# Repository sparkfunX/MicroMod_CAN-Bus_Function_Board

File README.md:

SparkX MicroMod CAN Bus Function Board
========================================

[*MicroMod CAN Bus Function Board (SPX-21775)*](https://www.sparkfun.com/products/21775)

Controller Area Network (CAN bus) continues to be a popular communication standard in all sorts of applications from passenger vehicles to lighting control and building automation. This MicroMod function board allows you to add CAN networking to your next MicroMod project. 

The CAN communications are handled by the MCP2515 stand-alone CAN controller paired up with an MCP2551 high-speed CAN transceiver. The MCP2515 is a very popular IC for CAN Bus, which means there are a variety of Arduino libraries already available. We quite like Sandeep Mistry's [arduino-CAN Library](https://github.com/sandeepmistry/arduino-CAN). If your processor board has a built-in CAN controller, however, you can change a solder jumper on the bottom of the board to address the CAN transceiver directly, bypassing the MCP2515.

Repository Contents
-------------------

* **/Hardware** - Eagle design files (.brd, .sch)
* **/Production** - Production panel files (.brd)

Documentation
--------------
  
* **[MCP2515 Datasheet](https://cdn.sparkfun.com/assets/1/0/e/4/0/MCP2515-Family-Data-Sheet-DS20001801K.pdf)** -MCP2515 Stand-Alone CAN Controller
* **[MCP2551 Datasheet](https://cdn.sparkfun.com/assets/8/d/9/b/8/20001667G.pdf)** -MCP2551 High-Speed CAN Transceiver
* **[Arduino Library](https://github.com/sandeepmistry/arduino-CAN)** -Sandeep Mistry's arduino-CAN library

License Information
-------------------

This product is _**open source**_! 

Please review the LICENSE.md file for license information. 

If you have any questions or concerns on licensing, please contact technical support on our [SparkFun forums](https://forum.sparkfun.com/viewforum.php?f=152).

Distributed as-is; no warranty is given.

- Your friends at SparkFun.

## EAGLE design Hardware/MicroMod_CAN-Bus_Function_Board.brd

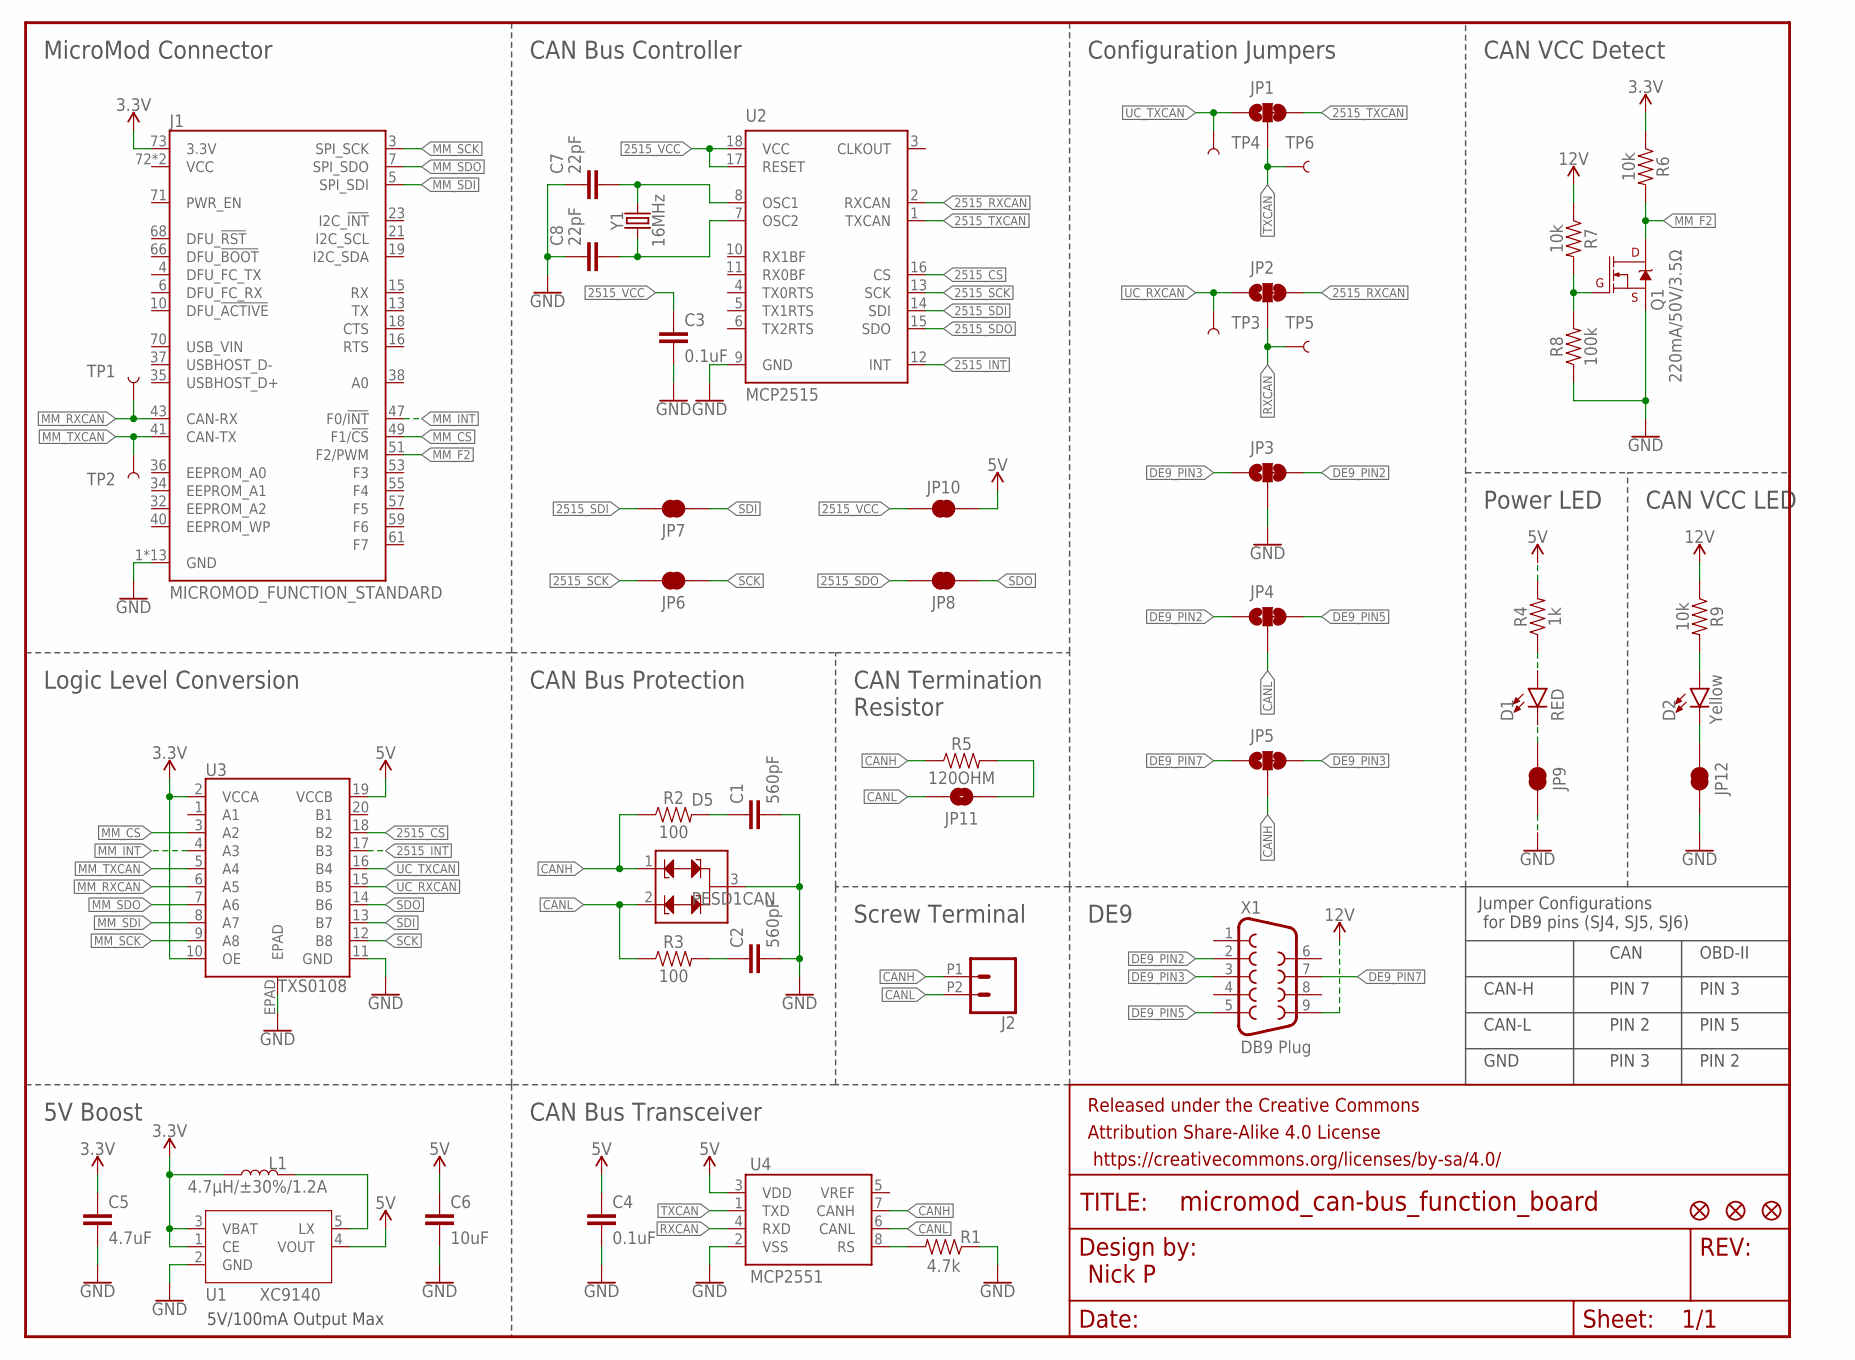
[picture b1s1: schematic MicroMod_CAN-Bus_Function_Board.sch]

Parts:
C1, C2: 560pF; 0603
C3, C4: 0.1uF; 0603
C5: 4.7uF; 0603
C6: 10uF; 0603
C7, C8: 22pF; 0603
D1: RED; LED-0603
D2: Yellow; LED-0603
D5: PESD1CAN; SOT23-3
FD1, FD2: FIDUCIAL1X2; FIDUCIAL-1X2
FD3: FIDUCIAL0.2MM; FIDUCIAL-0.2MM
FRAME1: FRAME-LETTER; CREATIVE_COMMONS
J1: MICROMOD_FUNCTION_STANDARD; M.2-CARD-E-22_FUNCTION_STANDARD
J2: CONN_022.54MM_SCREWTERM; 1X02_2.54_SCREWTERM
JP1, JP2, JP3, JP4, JP5: JUMPER-SMT_3_1-NC_TRACE_NO-SILK; SMT-JUMPER_3_1-NC_TRACE_NO-SILK
JP6, JP7, JP8, JP9, JP10, JP12: JUMPER-SMT_2_NC_TRACE_NO-SILK; SMT-JUMPER_2_NC_TRACE_NO-SILK
JP11: JUMPER-SMT_2_NO_NO-SILK; SMT-JUMPER_2_NO_NO-SILK
L1: 4.7µH/±30%/1.2A; INDUCTOR_4.7UH
Q1: 220mA/50V/3.5Ω; SOT23-3
R1: 4.7k; 0603
R2, R3: 100; 0603
R4: 1k; 0603
R5: 120OHM; 0603
R6, R7, R9: 10k; 0603
R8: 100k; 0603
TP1, TP2, TP3, TP4, TP5, TP6: TEST-POINT3; PAD.03X.03
U1: XC9140; SOT23-5
U2: MCP2515; SO18W
U3: TXS0108; VFQFN-20
U4: MCP2551; SO08
X1: DB9 Plug; DB9_MALE
Y1: 16MHz; CRYSTAL-SMD-2.0X1.6MM

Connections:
3.3V: C5.1, J1.73 (3.3V), L1.P$2 (2), R6.1, U1.1 (CE), U1.3 (VBAT), U3.2 (VCCA), U3.10 (OE)
5V: C4.1, C6.1, JP10.2, R4.2, U1.4 (VOUT), U3.19 (VCCB), U4.3 (VDD)
12V: R7.1, R9.1, X1.9
2515_CS: U2.16 (CS), U3.18 (B2)
2515_INT: U2.12 (INT), U3.17 (B3)
2515_RXCAN: JP2.3, U2.2 (RXCAN)
2515_SCK: JP6.2, U2.13 (SCK)
2515_SDI: JP7.2, U2.14 (SDI)
2515_SDO: JP8.2, U2.15 (SDO)
2515_TXCAN: JP1.3, U2.1 (TXCAN)
2515_VCC: C3.1, JP10.1, U2.17 (RESET), U2.18 (VCC)
CANH: D5.1, J2.P1 (1), JP5.2, R2.1, R5.1, U4.7 (CANH)
CANL: D5.2, J2.P2 (2), JP4.2, JP11.2, R3.1, U4.6 (CANL)
DE9_PIN2: JP3.3, JP4.1, X1.2
DE9_PIN3: JP3.1, JP5.3, X1.3
DE9_PIN5: JP4.3, X1.5
DE9_PIN7: JP5.1, X1.7
GND: C1.2, C2.2, C3.2, C4.2, C5.2, C6.2, C7.1, C8.1, D5.3, J1.1 (GND), J1.2 (GND), J1.8 (GND), J1.33 (GND), J1.39 (GND), J1.45 (GND), J1.75 (GND), J1.GND1 (GND), J1.GND2 (GND), J1.GND3 (GND), J1.GND4 (GND), J1.GND5 (GND), J1.GND6 (GND), JP3.2, JP9.2, JP12.2, Q1.2 (S), R1.1, R8.1, U1.2 (GND), U2.9 (GND), U3.11 (GND), U4.2 (VSS)
MM_CS: J1.49 (F1/!CS!), U3.3 (A2)
MM_F2: J1.51 (F2/PWM), Q1.3 (D), R6.2
MM_INT: J1.47 (F0/!INT!), U3.4 (A3)
MM_RXCAN: J1.43 (CAN-RX), TP1.1, U3.6 (A5)
MM_SCK: J1.3 (SPI_SCK), U3.9 (A8)
MM_SDI: J1.5 (SPI_SDI), U3.8 (A7)
MM_SDO: J1.7 (SPI_SDO), U3.7 (A6)
MM_TXCAN: J1.41 (CAN-TX), TP2.1, U3.5 (A4)
unnamed: C1.1, R2.2
unnamed: C2.1, R3.2
unnamed: C7.2, U2.8 (OSC1), Y1.3 (2)
unnamed: L1.P$1 (1), U1.5 (LX)
unnamed: C8.2, U2.7 (OSC2), Y1.1
unnamed: JP11.1, R5.2
unnamed: D1.C, JP9.1
unnamed: D1.A, R4.1
unnamed: R1.2, U4.8 (RS)
unnamed: Q1.1 (G), R7.2, R8.2
unnamed: D2.A, R9.2
unnamed: D2.C, JP12.1
RXCAN: JP2.2, TP5.1, U4.4 (RXD)
SCK: JP6.1, U3.12 (B8)
SDI: JP7.1, U3.13 (B7)
SDO: JP8.1, U3.14 (B6)
TXCAN: JP1.2, TP6.1, U4.1 (TXD)
UC_RXCAN: JP2.1, TP3.1, U3.15 (B5)
UC_TXCAN: JP1.1, TP4.1, U3.16 (B4)

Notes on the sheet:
CAN
OBD-II
CAN-H
CAN-L
GND
PIN 5
PIN 2
PIN 3
PIN 7
Jumper Configurations for DB9 pins (SJ4, SJ5, SJ6)
5V/100mA Output Max
MicroMod Connector
CAN Bus Controller
Configuration Jumpers
CAN VCC Detect
Power LED
DE9
Screw Terminal
CAN Termination Resistor
CAN Bus Protection
Logic Level Conversion
5V Boost
CAN Bus Transceiver
CAN VCC LED
Nick P

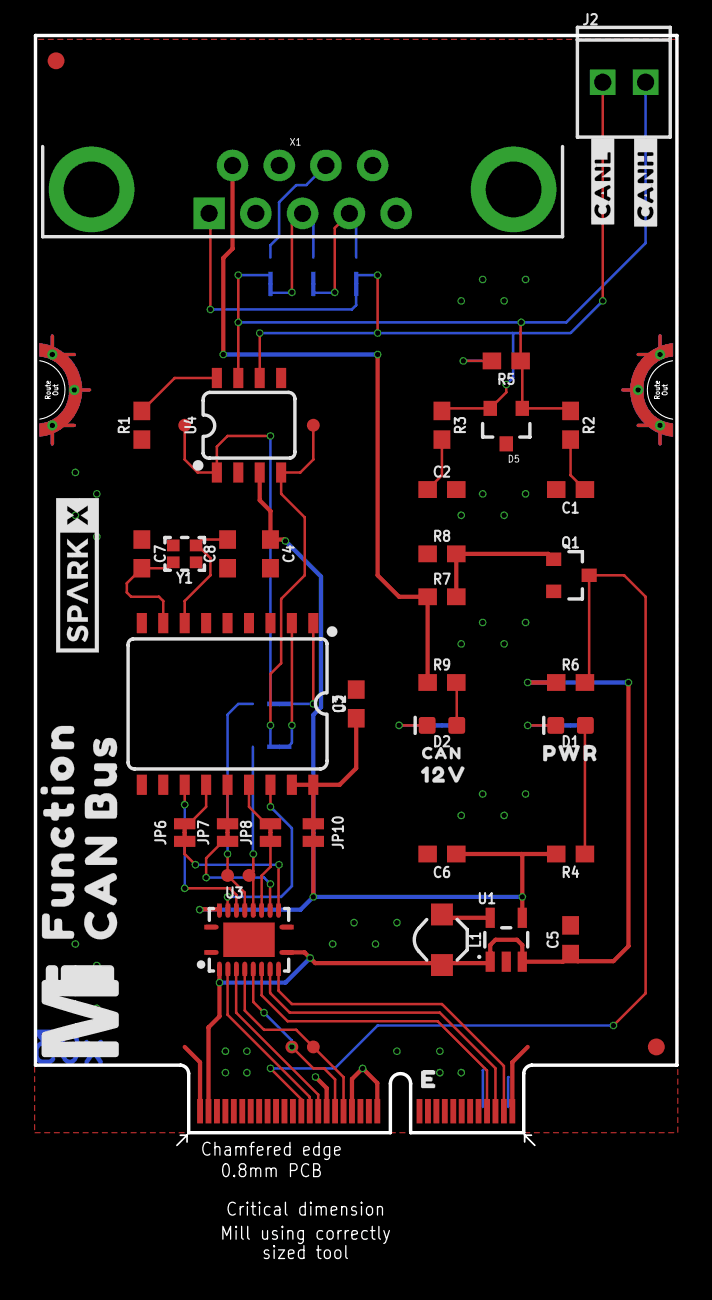
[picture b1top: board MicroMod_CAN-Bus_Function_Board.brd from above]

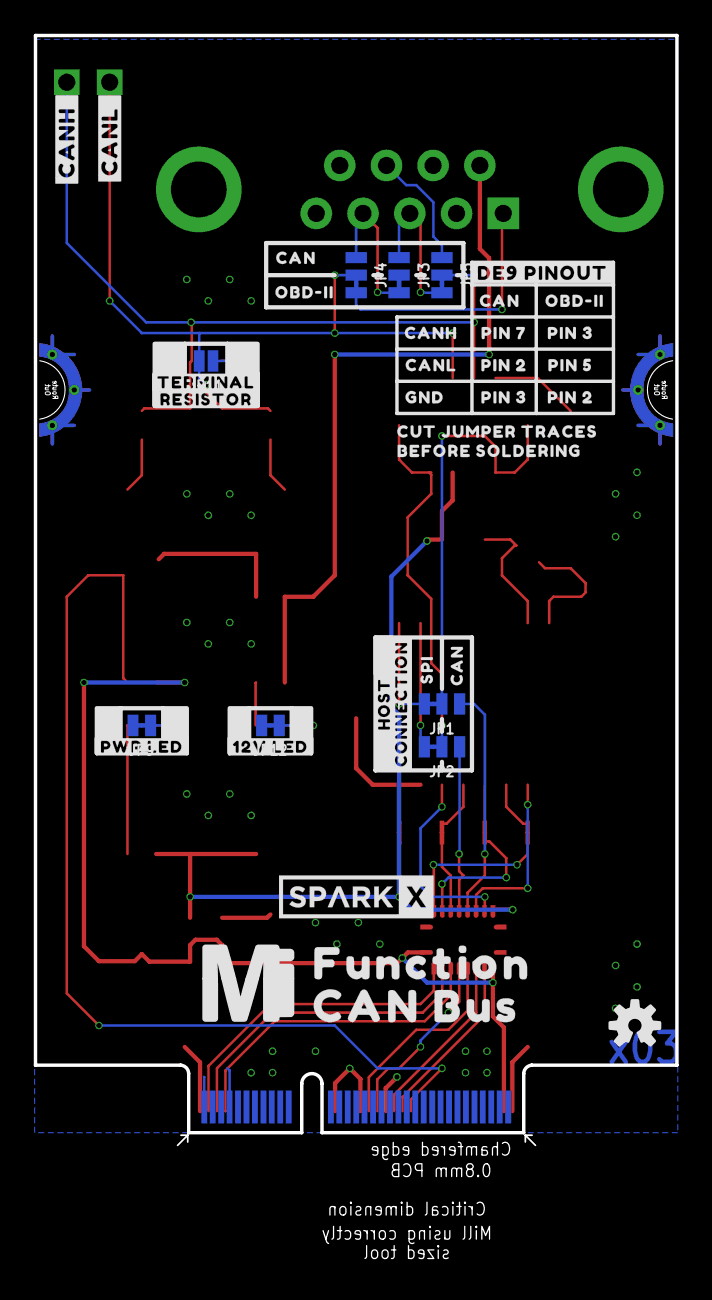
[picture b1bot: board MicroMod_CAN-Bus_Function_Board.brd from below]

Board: 4 copper layers, 38.0 x 72.8 mm, 93 parts (39 on the bottom side), 45 nets.

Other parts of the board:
LOGO2: SPECIAL_INSTRUCTIONS-ORDERING; ORDERING_INSTRUCTIONS
U$1, U$36: MICROMOD_MI_LOGO_1
U$2, U$38: FUNCTION0
U$3, U$37: CAN_BUS0
U$4, U$39: SPARKX-MEDIUM
U$5, U$31: #CANH_#0
U$6, U$30: #CANL_#0
U$7: PWR0
U$8, U$18, U$27, U$28: CAN0
U$9: 12V0
U$10: #TERMINAL#0
U$11: #RESISTOR#0
U$12: #PWR_LED#0
U$13: #12V_LED#0
U$14: CUT_JUMPER_TRACES0
U$15: #DE9_PINOUT#0
U$16: BEFORE_SOLDERING0
U$17: GND0
U$19, U$26: OBD#II0
U$20: PIN_70
U$21, U$22: PIN_20
U$23, U$24: PIN_30
U$25: PIN_50
U$29: SPI0
U$32: CANH0
U$33: CANL0
U$34: #HOST#0
U$35: #CONNECTION#0
U$40: OSHW-LOGO-S

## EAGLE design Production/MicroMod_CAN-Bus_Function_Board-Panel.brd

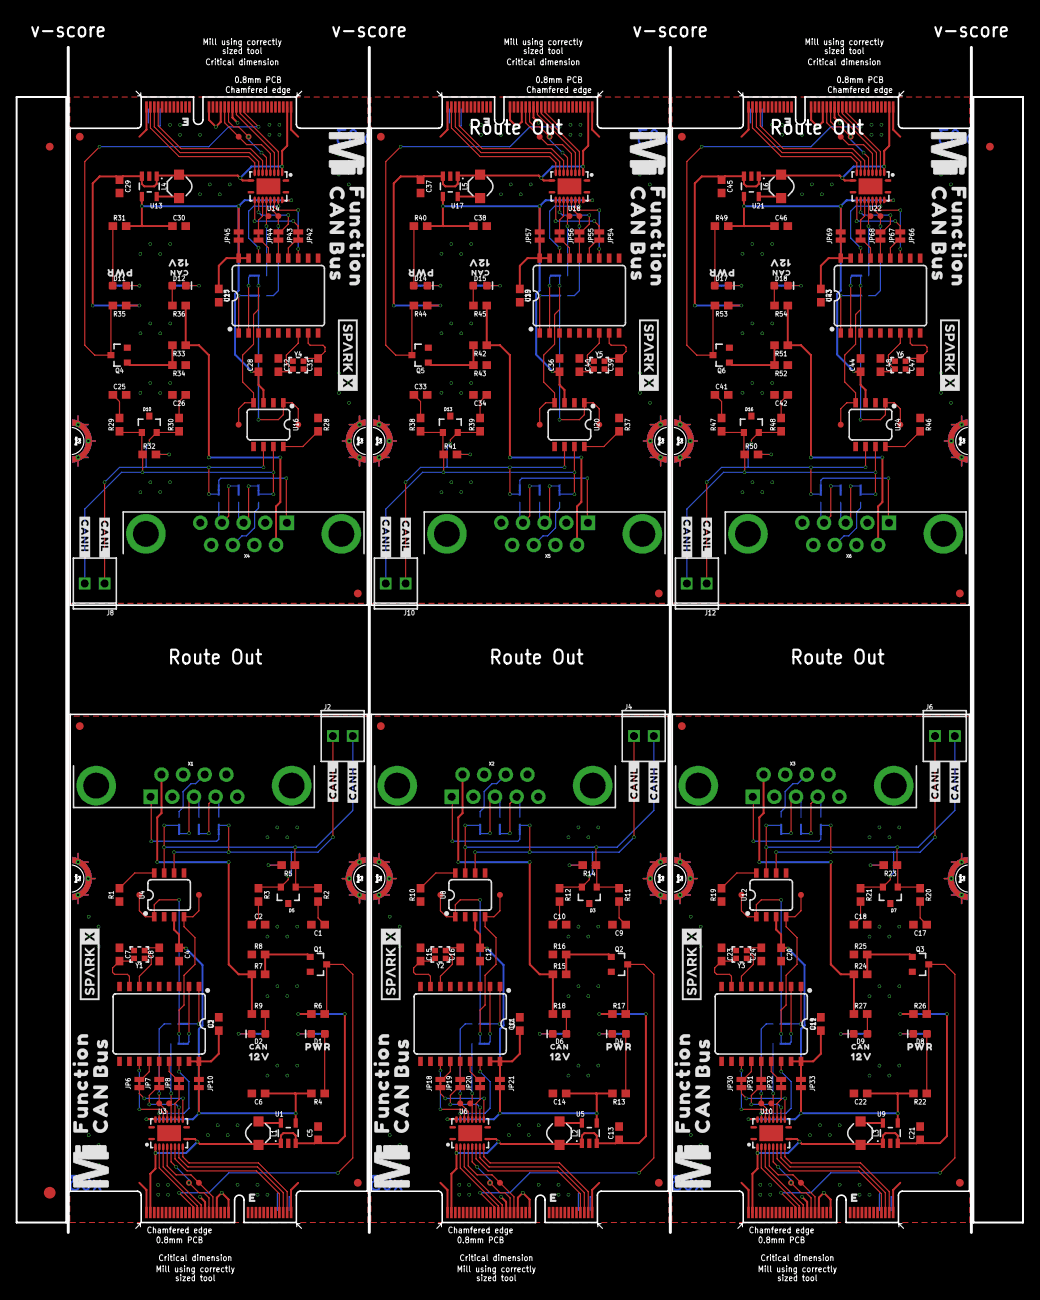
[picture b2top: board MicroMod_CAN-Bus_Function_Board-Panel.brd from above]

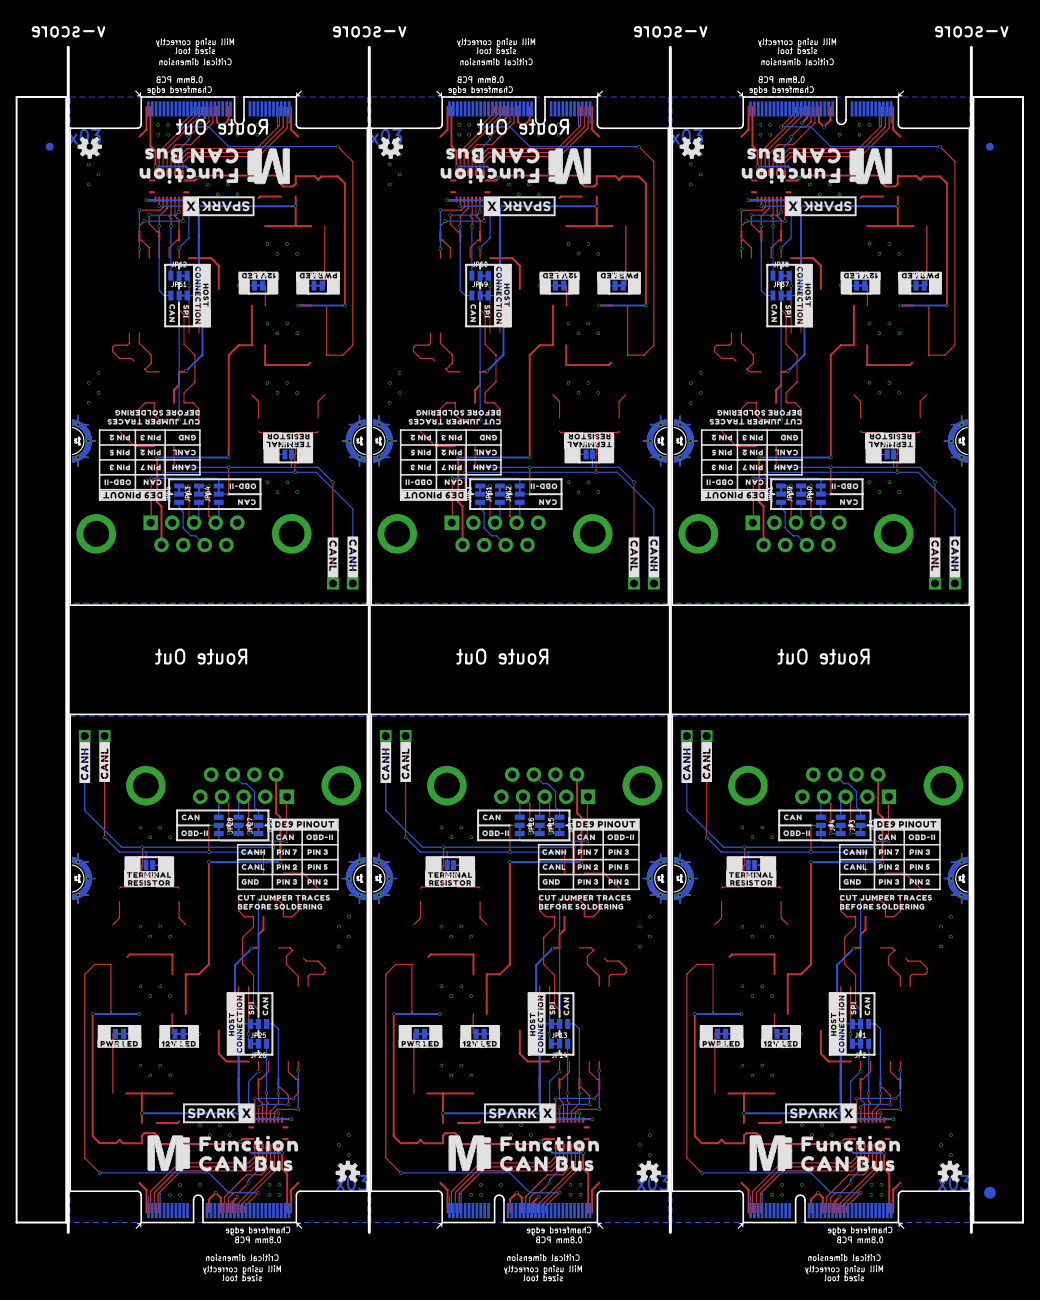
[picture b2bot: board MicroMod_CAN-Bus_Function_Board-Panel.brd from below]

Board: 4 copper layers, 128.6 x 161.9 mm, 552 parts (237 on the bottom side), 270 nets.

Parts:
C1, C2, C9, C10, C17, C18, C25, C26, C33, C34, C41, C42: 560pF; 0603
C3, C4, C11, C12, C19, C20, C27, C28, C35, C36, C43, C44: 0.1uF; 0603
C5, C13, C21, C29, C37, C45: 4.7uF; 0603
C6, C14, C22, C30, C38, C46: 10uF; 0603
C7, C8, C15, C16, C23, C24, C31, C32, C39, C40, C47, C48: 22pF; 0603
D1, D4, D8, D11, D14, D17: RED; LED-0603
D2, D6, D9, D12, D15, D18: Yellow; LED-0603
D3, D5, D7, D10, D13, D16: PESD1CAN; SOT23-3
E$1, E$2, E$3, E$4: FIDUCIAL-1X2
E$5, E$6: FIDUCIAL-1.5X3
FD1, FD2, FD4, FD5, FD7, FD8, FD10, FD11, FD13, FD14, FD16, FD17: FIDUCIAL1X2; FIDUCIAL-1X2
FD3, FD6, FD9, FD12, FD15, FD18: FIDUCIAL0.2MM; FIDUCIAL-0.2MM
J1, J3, J5, J7, J9, J11: MICROMOD_FUNCTION_STANDARD; M.2-CARD-E-22_FUNCTION_STANDARD
J2, J4, J6, J8, J10, J12: 1X02_2.54_SCREWTERM
JP1, JP2, JP3, JP4, JP5, JP13, JP14, JP15, JP16, JP17, JP25, JP26, JP27, JP28, JP29, JP37, JP38, JP39, JP40, JP41, JP49, JP50, JP51, JP52, JP53, JP61, JP62, JP63, JP64, JP65: JUMPER-SMT_3_1-NC_TRACE_NO-SILK; SMT-JUMPER_3_1-NC_TRACE_NO-SILK
JP6, JP7, JP8, JP9, JP10, JP12, JP18, JP19, JP20, JP21, JP22, JP24, JP30, JP31, JP32, JP33, JP34, JP36, JP42, JP43, JP44, JP45, JP46, JP48, JP54, JP55, JP56, JP57, JP58, JP60, JP66, JP67, JP68, JP69, JP70, JP72: JUMPER-SMT_2_NC_TRACE_NO-SILK; SMT-JUMPER_2_NC_TRACE_NO-SILK
JP11, JP23, JP35, JP47, JP59, JP71: JUMPER-SMT_2_NO_NO-SILK; SMT-JUMPER_2_NO_NO-SILK
L1, L2, L3, L4, L5, L6: 4.7µH/±30%/1.2A; INDUCTOR_4.7UH
Q1, Q2, Q3, Q4, Q5, Q6: 220mA/50V/3.5Ω; SOT23-3
R1, R10, R19, R28, R37, R46: 4.7k; 0603
R2, R3, R11, R12, R20, R21, R29, R30, R38, R39, R47, R48: 100; 0603
R4, R13, R22, R31, R40, R49: 1k; 0603
R5, R14, R23, R32, R41, R50: 120OHM; 0603
R6, R7, R9, R15, R17, R18, R24, R26, R27, R33, R35, R36, R42, R44, R45, R51, R53, R54: 10k; 0603
R8, R16, R25, R34, R43, R52: 100k; 0603
TP1, TP2, TP3, TP4, TP5, TP6, TP7, TP8, TP9, TP10, TP11, TP12, TP13, TP14, TP15, TP16, TP17, TP18, TP19, TP20, TP21, TP22, TP23, TP24, TP25, TP26, TP27, TP28, TP29, TP30, TP31, TP32, TP33, TP34, TP35, TP36: TEST-POINT3; PAD.03X.03
U1, U5, U9, U13, U17, U21: XC9140; SOT23-5
U2, U7, U11, U15, U19, U23: MCP2515; SO18W
U3, U6, U10, U14, U18, U22: TXS0108; VFQFN-20
U4, U8, U12, U16, U20, U24: MCP2551; SO08
U$1, U$36, U$41, U$75, U$81, U$115, U$121, U$155, U$161, U$195, U$201, U$235: MICROMOD_MI_LOGO_1
U$2, U$38, U$42, U$77, U$82, U$117, U$122, U$157, U$162, U$197, U$202, U$237: FUNCTION0
U$3, U$37, U$43, U$76, U$83, U$116, U$123, U$156, U$163, U$196, U$203, U$236: CAN_BUS0
U$4, U$39, U$79, U$80, U$119, U$120, U$159, U$160, U$199, U$200, U$239, U$240: SPARKX-MEDIUM
U$5, U$31, U$52, U$66, U$92, U$106, U$132, U$146, U$172, U$186, U$212, U$226: #CANH_#0
U$6, U$30, U$53, U$65, U$93, U$105, U$133, U$145, U$173, U$185, U$213, U$225: #CANL_#0
U$7, U$54, U$94, U$134, U$174, U$214: PWR0
U$8, U$18, U$27, U$28, U$55, U$62, U$63, U$67, U$95, U$102, U$103, U$107, U$135, U$142, U$143, U$147, U$175, U$182, U$183, U$187, U$215, U$222, U$223, U$227: CAN0
U$9, U$56, U$96, U$136, U$176, U$216: 12V0
U$10, U$57, U$97, U$137, U$177, U$217: #TERMINAL#0
U$11, U$58, U$98, U$138, U$178, U$218: #RESISTOR#0
U$12, U$59, U$99, U$139, U$179, U$219: #PWR_LED#0
U$13, U$60, U$100, U$140, U$180, U$220: #12V_LED#0
U$14, U$71, U$111, U$151, U$191, U$231: CUT_JUMPER_TRACES0
U$15, U$70, U$110, U$150, U$190, U$230: #DE9_PINOUT#0
U$16, U$72, U$112, U$152, U$192, U$232: BEFORE_SOLDERING0
U$17, U$44, U$84, U$124, U$164, U$204: GND0
U$19, U$26, U$45, U$61, U$85, U$101, U$125, U$141, U$165, U$181, U$205, U$221: OBD#II0
U$20, U$46, U$86, U$126, U$166, U$206: PIN_70
U$21, U$22, U$47, U$48, U$87, U$88, U$127, U$128, U$167, U$168, U$207, U$208: PIN_20
U$23, U$24, U$49, U$50, U$89, U$90, U$129, U$130, U$169, U$170, U$209, U$210: PIN_30
U$25, U$51, U$91, U$131, U$171, U$211: PIN_50
U$29, U$64, U$104, U$144, U$184, U$224: SPI0
U$32, U$68, U$108, U$148, U$188, U$228: CANH0
U$33, U$69, U$109, U$149, U$189, U$229: CANL0
U$34, U$73, U$113, U$153, U$193, U$233: #HOST#0
U$35, U$74, U$114, U$154, U$194, U$234: #CONNECTION#0
U$40, U$78, U$118, U$158, U$198, U$238: OSHW-LOGO-S
X1, X2, X3, X4, X5, X6: DB9 Plug; DB9_MALE
Y1, Y2, Y3, Y4, Y5, Y6: 16MHz; CRYSTAL-SMD-2.0X1.6MM

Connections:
3.3V: C5.1, J1.73, L1.P$2, R6.1, U1.1, U1.3, U3.2, U3.10
3.3V1: C13.1, J3.73, L2.P$2, R17.1, U5.1, U5.3, U6.2, U6.10
3.3V2: C21.1, J5.73, L3.P$2, R26.1, U9.1, U9.3, U10.2, U10.10
3.3V3: C29.1, J7.73, L4.P$2, R35.1, U13.1, U13.3, U14.2, U14.10
3.3V4: C37.1, J9.73, L5.P$2, R44.1, U17.1, U17.3, U18.2, U18.10
3.3V5: C45.1, J11.73, L6.P$2, R53.1, U21.1, U21.3, U22.2, U22.10
5V: C4.1, C6.1, JP10.2, R4.2, U1.4, U3.19, U4.3
5V1: C12.1, C14.1, JP21.2, R13.2, U5.4, U6.19, U8.3
5V2: C20.1, C22.1, JP33.2, R22.2, U9.4, U10.19, U12.3
5V3: C28.1, C30.1, JP45.2, R31.2, U13.4, U14.19, U16.3
5V4: C36.1, C38.1, JP57.2, R40.2, U17.4, U18.19, U20.3
5V5: C44.1, C46.1, JP69.2, R49.2, U21.4, U22.19, U24.3
12V: R7.1, R9.1, X1.9
12V1: R15.1, R18.1, X2.9
12V2: R24.1, R27.1, X3.9
12V3: R33.1, R36.1, X4.9
12V4: R42.1, R45.1, X5.9
12V5: R51.1, R54.1, X6.9
2515_CS: U2.16, U3.18
2515_CS1: U6.18, U7.16
2515_CS2: U10.18, U11.16
2515_CS3: U14.18, U15.16
2515_CS4: U18.18, U19.16
2515_CS5: U22.18, U23.16
2515_INT: U2.12, U3.17
2515_INT1: U6.17, U7.12
2515_INT2: U10.17, U11.12
2515_INT3: U14.17, U15.12
2515_INT4: U18.17, U19.12
2515_INT5: U22.17, U23.12
2515_RXCAN: JP2.3, U2.2
2515_RXCAN1: JP14.3, U7.2
2515_RXCAN2: JP26.3, U11.2
2515_RXCAN3: JP38.3, U15.2
2515_RXCAN4: JP50.3, U19.2
2515_RXCAN5: JP62.3, U23.2
2515_SCK: JP6.2, U2.13
2515_SCK1: JP18.2, U7.13
2515_SCK2: JP30.2, U11.13
2515_SCK3: JP42.2, U15.13
2515_SCK4: JP54.2, U19.13
2515_SCK5: JP66.2, U23.13
2515_SDI: JP7.2, U2.14
2515_SDI1: JP19.2, U7.14
2515_SDI2: JP31.2, U11.14
2515_SDI3: JP43.2, U15.14
2515_SDI4: JP55.2, U19.14
2515_SDI5: JP67.2, U23.14
2515_SDO: JP8.2, U2.15
2515_SDO1: JP20.2, U7.15
2515_SDO2: JP32.2, U11.15
2515_SDO3: JP44.2, U15.15
2515_SDO4: JP56.2, U19.15
2515_SDO5: JP68.2, U23.15
2515_TXCAN: JP1.3, U2.1
2515_TXCAN1: JP13.3, U7.1
2515_TXCAN2: JP25.3, U11.1
2515_TXCAN3: JP37.3, U15.1
2515_TXCAN4: JP49.3, U19.1
2515_TXCAN5: JP61.3, U23.1
2515_VCC: C3.1, JP10.1, U2.17, U2.18
2515_VCC1: C11.1, JP21.1, U7.17, U7.18
2515_VCC2: C19.1, JP33.1, U11.17, U11.18
2515_VCC3: C27.1, JP45.1, U15.17, U15.18
2515_VCC4: C35.1, JP57.1, U19.17, U19.18
2515_VCC5: C43.1, JP69.1, U23.17, U23.18
CANH: D5.1, J2.P1, JP5.2, R2.1, R5.1, U4.7
CANH1: D3.1, J4.P1, JP17.2, R11.1, R14.1, U8.7
CANH2: D7.1, J6.P1, JP29.2, R20.1, R23.1, U12.7
CANH3: D10.1, J8.P1, JP41.2, R29.1, R32.1, U16.7
CANH4: D13.1, J10.P1, JP53.2, R38.1, R41.1, U20.7
CANH5: D16.1, J12.P1, JP65.2, R47.1, R50.1, U24.7
CANL: D5.2, J2.P2, JP4.2, JP11.2, R3.1, U4.6
CANL1: D3.2, J4.P2, JP16.2, JP23.2, R12.1, U8.6
CANL2: D7.2, J6.P2, JP28.2, JP35.2, R21.1, U12.6
CANL3: D10.2, J8.P2, JP40.2, JP47.2, R30.1, U16.6
CANL4: D13.2, J10.P2, JP52.2, JP59.2, R39.1, U20.6
CANL5: D16.2, J12.P2, JP64.2, JP71.2, R48.1, U24.6
DE9_PIN1: JP15.3, JP16.1, X2.2
DE9_PIN2: JP3.3, JP4.1, X1.2
DE9_PIN3: JP3.1, JP5.3, X1.3
DE9_PIN4: JP15.1, JP17.3, X2.3
DE9_PIN5: JP4.3, X1.5
DE9_PIN6: JP16.3, X2.5
DE9_PIN7: JP5.1, X1.7
DE9_PIN8: JP17.1, X2.7
DE9_PIN9: JP27.3, JP28.1, X3.2
DE9_PIN10: JP27.1, JP29.3, X3.3
DE9_PIN11: JP28.3, X3.5
DE9_PIN12: JP29.1, X3.7
DE9_PIN13: JP39.3, JP40.1, X4.2
DE9_PIN14: JP39.1, JP41.3, X4.3
DE9_PIN15: JP40.3, X4.5
DE9_PIN16: JP41.1, X4.7
DE9_PIN17: JP51.3, JP52.1, X5.2
DE9_PIN18: JP51.1, JP53.3, X5.3
DE9_PIN19: JP52.3, X5.5
DE9_PIN20: JP53.1, X5.7
DE9_PIN21: JP63.3, JP64.1, X6.2
DE9_PIN22: JP63.1, JP65.3, X6.3
DE9_PIN23: JP64.3, X6.5
DE9_PIN24: JP65.1, X6.7
GND: C1.2, C2.2, C3.2, C4.2, C5.2, C6.2, C7.1, C8.1, D5.3, J1.1, J1.2, J1.8, J1.33, J1.39, J1.45, J1.75, J1.GND1, J1.GND2, J1.GND3, J1.GND4, J1.GND5, J1.GND6, JP3.2, JP9.2, JP12.2, Q1.2, R1.1, R8.1, U1.2, U2.9, U3.11, U4.2
GND1: C9.2, C10.2, C11.2, C12.2, C13.2, C14.2, C15.1, C16.1, D3.3, J3.1, J3.2, J3.8, J3.33, J3.39, J3.45, J3.75, J3.GND1, J3.GND2, J3.GND3, J3.GND4, J3.GND5, J3.GND6, JP15.2, JP22.2, JP24.2, Q2.2, R10.1, R16.1, U5.2, U6.11, U7.9, U8.2
GND2: C17.2, C18.2, C19.2, C20.2, C21.2, C22.2, C23.1, C24.1, D7.3, J5.1, J5.2, J5.8, J5.33, J5.39, J5.45, J5.75, J5.GND1, J5.GND2, J5.GND3, J5.GND4, J5.GND5, J5.GND6, JP27.2, JP34.2, JP36.2, Q3.2, R19.1, R25.1, U9.2, U10.11, U11.9, U12.2
GND3: C25.2, C26.2, C27.2, C28.2, C29.2, C30.2, C31.1, C32.1, D10.3, J7.1, J7.2, J7.8, J7.33, J7.39, J7.45, J7.75, J7.GND1, J7.GND2, J7.GND3, J7.GND4, J7.GND5, J7.GND6, JP39.2, JP46.2, JP48.2, Q4.2, R28.1, R34.1, U13.2, U14.11, U15.9, U16.2
GND4: C33.2, C34.2, C35.2, C36.2, C37.2, C38.2, C39.1, C40.1, D13.3, J9.1, J9.2, J9.8, J9.33, J9.39, J9.45, J9.75, J9.GND1, J9.GND2, J9.GND3, J9.GND4, J9.GND5, J9.GND6, JP51.2, JP58.2, JP60.2, Q5.2, R37.1, R43.1, U17.2, U18.11, U19.9, U20.2
GND5: C41.2, C42.2, C43.2, C44.2, C45.2, C46.2, C47.1, C48.1, D16.3, J11.1, J11.2, J11.8, J11.33, J11.39, J11.45, J11.75, J11.GND1, J11.GND2, J11.GND3, J11.GND4, J11.GND5, J11.GND6, JP63.2, JP70.2, JP72.2, Q6.2, R46.1, R52.1, U21.2, U22.11, U23.9, U24.2
MM_CS: J1.49, U3.3
MM_CS1: J3.49, U6.3
MM_CS2: J5.49, U10.3
MM_CS3: J7.49, U14.3
MM_CS4: J9.49, U18.3
MM_CS5: J11.49, U22.3
MM_F1: J3.51, Q2.3, R17.2
MM_F2: J1.51, Q1.3, R6.2
MM_F3: J5.51, Q3.3, R26.2
MM_F4: J7.51, Q4.3, R35.2
MM_F5: J9.51, Q5.3, R44.2
MM_F6: J11.51, Q6.3, R53.2
MM_INT: J1.47, U3.4
MM_INT1: J3.47, U6.4
MM_INT2: J5.47, U10.4
MM_INT3: J7.47, U14.4
MM_INT4: J9.47, U18.4
MM_INT5: J11.47, U22.4
MM_RXCAN: J1.43, TP1.1, U3.6
MM_RXCAN1: J3.43, TP7.1, U6.6
MM_RXCAN2: J5.43, TP13.1, U10.6
MM_RXCAN3: J7.43, TP19.1, U14.6
MM_RXCAN4: J9.43, TP25.1, U18.6
MM_RXCAN5: J11.43, TP31.1, U22.6
MM_SCK: J1.3, U3.9
MM_SCK1: J3.3, U6.9
MM_SCK2: J5.3, U10.9
MM_SCK3: J7.3, U14.9
MM_SCK4: J9.3, U18.9
MM_SCK5: J11.3, U22.9
MM_SDI: J1.5, U3.8
MM_SDI1: J3.5, U6.8
MM_SDI2: J5.5, U10.8
MM_SDI3: J7.5, U14.8
MM_SDI4: J9.5, U18.8
MM_SDI5: J11.5, U22.8
MM_SDO: J1.7, U3.7
MM_SDO1: J3.7, U6.7
MM_SDO2: J5.7, U10.7
MM_SDO3: J7.7, U14.7
MM_SDO4: J9.7, U18.7
MM_SDO5: J11.7, U22.7
MM_TXCAN: J1.41, TP2.1, U3.5
MM_TXCAN1: J3.41, TP8.1, U6.5
MM_TXCAN2: J5.41, TP14.1, U10.5
MM_TXCAN3: J7.41, TP20.1, U14.5
MM_TXCAN4: J9.41, TP26.1, U18.5
MM_TXCAN5: J11.41, TP32.1, U22.5
unnamed: C1.1, R2.2
unnamed: C2.1, R3.2
unnamed: C7.2, U2.8, Y1.3
unnamed: L1.P$1, U1.5
unnamed: C8.2, U2.7, Y1.1
unnamed: JP11.1, R5.2
unnamed: D1.C, JP9.1
unnamed: D1.A, R4.1
unnamed: R1.2, U4.8
unnamed: Q1.1, R7.2, R8.2
unnamed: D2.A, R9.2
unnamed: D2.C, JP12.1
unnamed: R10.2, U8.8
unnamed: C9.1, R11.2
unnamed: C10.1, R12.2
unnamed: L2.P$1, U5.5
unnamed: C15.2, U7.8, Y2.3
unnamed: C16.2, U7.7, Y2.1
unnamed: D4.C, JP22.1
unnamed: D4.A, R13.1
unnamed: JP23.1, R14.2
unnamed: Q2.1, R15.2, R16.2
unnamed: D6.A, R18.2
unnamed: D6.C, JP24.1
unnamed: R19.2, U12.8
unnamed: C17.1, R20.2
unnamed: C18.1, R21.2
unnamed: L3.P$1, U9.5
unnamed: C23.2, U11.8, Y3.3
unnamed: C24.2, U11.7, Y3.1
unnamed: D8.C, JP34.1
unnamed: D8.A, R22.1
unnamed: JP35.1, R23.2
unnamed: Q3.1, R24.2, R25.2
unnamed: D9.A, R27.2
unnamed: D9.C, JP36.1
unnamed: R28.2, U16.8
unnamed: C25.1, R29.2
unnamed: C26.1, R30.2
unnamed: L4.P$1, U13.5
unnamed: C31.2, U15.8, Y4.3
unnamed: C32.2, U15.7, Y4.1
unnamed: D11.C, JP46.1
unnamed: D11.A, R31.1
unnamed: JP47.1, R32.2
unnamed: Q4.1, R33.2, R34.2
unnamed: D12.A, R36.2
unnamed: D12.C, JP48.1
unnamed: R37.2, U20.8
unnamed: C33.1, R38.2
unnamed: C34.1, R39.2
unnamed: L5.P$1, U17.5
unnamed: C39.2, U19.8, Y5.3
unnamed: C40.2, U19.7, Y5.1
unnamed: D14.C, JP58.1
unnamed: D14.A, R40.1
unnamed: JP59.1, R41.2
unnamed: Q5.1, R42.2, R43.2
unnamed: D15.A, R45.2
unnamed: D15.C, JP60.1
unnamed: R46.2, U24.8
unnamed: C41.1, R47.2
unnamed: C42.1, R48.2
unnamed: L6.P$1, U21.5
unnamed: C47.2, U23.8, Y6.3
unnamed: C48.2, U23.7, Y6.1
unnamed: D17.C, JP70.1
unnamed: D17.A, R49.1
unnamed: JP71.1, R50.2
unnamed: Q6.1, R51.2, R52.2
unnamed: D18.A, R54.2
unnamed: D18.C, JP72.1
RXCAN: JP2.2, TP5.1, U4.4
RXCAN1: JP14.2, TP11.1, U8.4
RXCAN2: JP26.2, TP17.1, U12.4
RXCAN3: JP38.2, TP23.1, U16.4
RXCAN4: JP50.2, TP29.1, U20.4
RXCAN5: JP62.2, TP35.1, U24.4
SCK: JP6.1, U3.12
SCK1: JP18.1, U6.12
SCK2: JP30.1, U10.12
SCK3: JP42.1, U14.12
SCK4: JP54.1, U18.12
SCK5: JP66.1, U22.12
SDI: JP7.1, U3.13
SDI1: JP19.1, U6.13
SDI2: JP31.1, U10.13
SDI3: JP43.1, U14.13
SDI4: JP55.1, U18.13
SDI5: JP67.1, U22.13
SDO: JP8.1, U3.14
SDO1: JP20.1, U6.14
SDO2: JP32.1, U10.14
SDO3: JP44.1, U14.14
SDO4: JP56.1, U18.14
SDO5: JP68.1, U22.14
TXCAN: JP1.2, TP6.1, U4.1
TXCAN1: JP13.2, TP12.1, U8.1
TXCAN2: JP25.2, TP18.1, U12.1
TXCAN3: JP37.2, TP24.1, U16.1
TXCAN4: JP49.2, TP30.1, U20.1
TXCAN5: JP61.2, TP36.1, U24.1
UC_RXCAN: JP2.1, TP3.1, U3.15
UC_RXCAN1: JP14.1, TP9.1, U6.15
UC_RXCAN2: JP26.1, TP15.1, U10.15
UC_RXCAN3: JP38.1, TP21.1, U14.15
UC_RXCAN4: JP50.1, TP27.1, U18.15
UC_RXCAN5: JP62.1, TP33.1, U22.15
UC_TXCAN: JP1.1, TP4.1, U3.16
UC_TXCAN1: JP13.1, TP10.1, U6.16
UC_TXCAN2: JP25.1, TP16.1, U10.16
UC_TXCAN3: JP37.1, TP22.1, U14.16
UC_TXCAN4: JP49.1, TP28.1, U18.16
UC_TXCAN5: JP61.1, TP34.1, U22.16

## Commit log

2023-01-24 Up from laptop (might be crashing)
2023-01-31 Housekeeping
2023-05-24 Ready to go public

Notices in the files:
parts and their libraries:
SparkFun-DiscreteSemi: Licensing: Creative Commons ShareAlike 4.0 International - https://creativecommons.org/licenses/by-sa/4.0
SparkFun-Connectors: Licensing: CC v3.0 Share-Alike You are welcome to use this library for commercial purposes.
SparkFun-Aesthetics: Released under the Creative Commons
